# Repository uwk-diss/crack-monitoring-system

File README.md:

# Open Source Low-cost IoT Crack Monitoring Sensor System

## Introduction

Cracks in buildings and infrastructure can pose safety risks if left unmonitored. Traditional commercial solutions can be prohibitively expensive, so this project was created to provide a cost-effective alternative. Here, you will find open-source hardware designs, firmware, and backend software needed to set up a complete, network-connected crack monitoring solution.

This project provides two different sensor designs for monitoring the width of existing cracks:
- A 3D-printable long range **draw-wire sensor** using a magnetic encoder and custom PCB.
- A **digital dial indicator sensor (shahe sensor)** offering reliable and accurate readings using a off the shelf digital dial indictor of the brand SHAHE.

Both sensors are designed to operate on battery power with LoRaWAN connectivity, and a corresponding backend is provided to visualize data in real-time using MQTT, InfluxDB, and Grafana. The goal is to make structural health monitoring both accessible and affordable.

## Hardware Overview and Specifications

The main communication module for both sensors is the **Heltec WiFi LoRa 32 (V3)**, which supports a deep sleep current of approximately **21 µA**. Beyond the LoRa radio, it also integrates an OLED display and a Li-ion battery charging and protection circuit.

For the **draw-wire sensor**, the temperature, humidity, and hall angle sensors connect via I²C. Meanwhile, the **digital dial indicator sensor** uses a proprietary serial protocol, read through a customized USB OTG cable.

### Sensor specs:

| Parameter               | Draw-Wire Sensor | SHAHE Sensor |
|-------------------------|------------------|----------------|
| Measurement Range       | 55 mm            | 26 mm          |
| Resolution              | 16 µm            | 10 µm          |
| Absolute Accuracy       | 96 µm            | 10 µm          |
| Repeatability           | ±16 µm           | ±10 µm         |
| Temperature Dependence  | 5 µm/°C*         | 0 µm/°C        |
| Position drift          | yes**            | no             |
| Battery Life            | ~11 months       | ~11 months     |
| Material Cost (excluding VAT)         | ~€48.50          | ~€65           |

*Temperature compensation of the draw-wire sensor is not implemented yet.

**During a 7-week long-term test, the draw-wire sensor exhibited a permanent position offset of more than 0.1 mm. This requires further investigation.

## Communication and Backend
The sensor data is transmitted hourly via LoRaWAN. [The Things Network](https://www.thethingsnetwork.org/) can be used as a provider for the LoRaWAN backend, or a self-hosted version such as [Chripstack](https://www.chirpstack.io/).
The data must be transferred from the LoRaWAN backend to a dedicated server via MQTT and stored in a database ([InfluxDB](https://github.com/influxdata/influxdb)). A Grafana dashboard is used to visualise the data.

## Repository Overview

- **draw-wire-sensor/**  
  Contains the 3D-printable hardware design, a PCB project, and the firmware source code for the draw-wire sensor.
- **shahe-sensor/**  
  Provides the hardware documentation and firmware to integrate the commercially available Shahe digital indicator.
- **backend/**  
  Contains Docker configurations, scripts, and a Grafana dashboard for storing, processing, and visualizing crack measurements.

More information and detailed assembly as well as usage instructions can be found in the respective subfolders.

## Credits

We would like to acknowledge the following open-source software libraries and frameworks that have made this project possible:
- [heltec_esp32_lora_v3 by Rop Gonggrijp](https://github.com/ropg/heltec_esp32_lora_v3) for providing the easy to use Heltec WiFi LoRa 32(V3) library
- [LoRaWAN_ESP32 by Rop Gonggrijp](https://github.com/ropg/LoRaWAN_ESP32) for LoRaWAN persistence handling
- [RadioLib](https://github.com/jgromes/RadioLib) for LoRaWan communication handling
- [PlatformIO](https://platformio.org/) for easy firmware development and deployment
- [Arduino Core](https://github.com/arduino/Arduino) for base microcontroller support
- [Docker](https://www.docker.com/) for containerization
- [Grafana](https://grafana.com/) for data visualization
- [InfluxDB](https://www.influxdata.com/) for time-series database storage

## Disclaimer

This Project is not completely finalized and may undergo changes. Use at your own risk.

## License

This project is available under the [MIT License](./LICENSE).

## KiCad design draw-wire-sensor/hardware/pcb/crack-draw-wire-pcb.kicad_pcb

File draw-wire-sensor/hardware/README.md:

# Draw-Wire Crack Sensor Hardware

## Draw-Wire Sensor
[3D-model Onshape Link](https://cad.onshape.com/documents/727012fc8109642ef30e330c/w/04f195b811331b23b33eb80b/e/cc3c6dd55492ae3cabf4f177?renderMode=0&uiState=67e1a618d2f76412aff66577)

### Functionality

### Materials
- 3D printed parts (Spool, BearingHolder1, BearingHolder2)
- Hall sensor PCB
- 8x16x5 mm ball bearing
- 0.2x5x420 mm spring
- 2 mm steel rod (2 pcs. 12 mm, 2 pcs. 8 mm) e.g. a bicycle spoke
- 0.5 mm steel wire (100 mm)
- Diametrical magnet (6 mm diameter, 1 mm thick)
- M4x8 button head screw and M4 washer
- M4x30 screws (4 pcs.)
- Single screw terminal as wire stopper

### Tools
- 3D Printer
- Soldering iron, solder, flux, and solder wick
- Round-nose pliers
- Tongue-and-groove pliers
- 2 mm drill bit

### Assembly
1. Assemble the PCB.
2. Print the parts (100% infill, 0.1 mm layer height).
3. Insert (and glue) the magnet into the spool with maximum precision.
4. Press-fit the bearings into the bearing-holders.
5. Press-fit the steel rods into the spool and upper bearing-holder (you may need to slightly drill out the holes beforehand).
6. Bend the spring as shown in the picture using round-nose pliers.
7. Insert the spool and then the spring.
8. Add the lower bearing-holder and slightly tighten the button head screw on the bottom of the spool.

## Enclosure
[3D-model Onshape Link](https://cad.onshape.com/documents/93da92487be01dacccf96228/w/5f335a3fbf208dbb23918342/e/3e6e6e181994376e8e597439?renderMode=0&uiState=67e194bb183653275da219e5)

### Materials
- 3D printed enclosure (ASA)
- Acrylic glass (2 mm) or 3D printed lid
- Short M3 inserts (8 pcs.)
- Short M4 inserts (4 pcs.)
- Short M2 inserts (2 pcs.)
- M3x6 screws (8 pcs.)
- M2x5 screws (2 pcs.)
- EPDM sealing cord (255 mm)
- Rubber grommet
- Acrylic paint / conformal coating / 3D-print sealant
- Silicone grease

### Tools
- 3D Printer
- Soldering iron
- 3.5 mm drill bit and drill
- Cutter knife

### Assembly
1. Print the enclosure (100% infill, 0.15 mm layer height).
2. Seal the print with spray paint.
3. Print the lid template (0.5 mm).
4. Transfer the template to acrylic glass and cut out the outlines.
5. Drill 3.5 mm screw holes in the lid.
6. Use a soldering iron to melt in the inserts.
7. Lubricate the seal and the grommet with silicone grease and insert them.

## Additional information
- With a longer string multiple parallel cracks can be monitored at once

## Future Improvements / To-Dos / Ideas
- Create a parametric 3D design for the draw-wire sensor and the enclosure using FreeCAD.
- Add a 3D printable adapter for standalone use of the draw-wire sensor with standard AS5600/MT6701 modules.
- Investigate the impact of hall sensor magnet alignment on accuracy and hysteresis.
- Further investigate the permanent drift of the sensor position

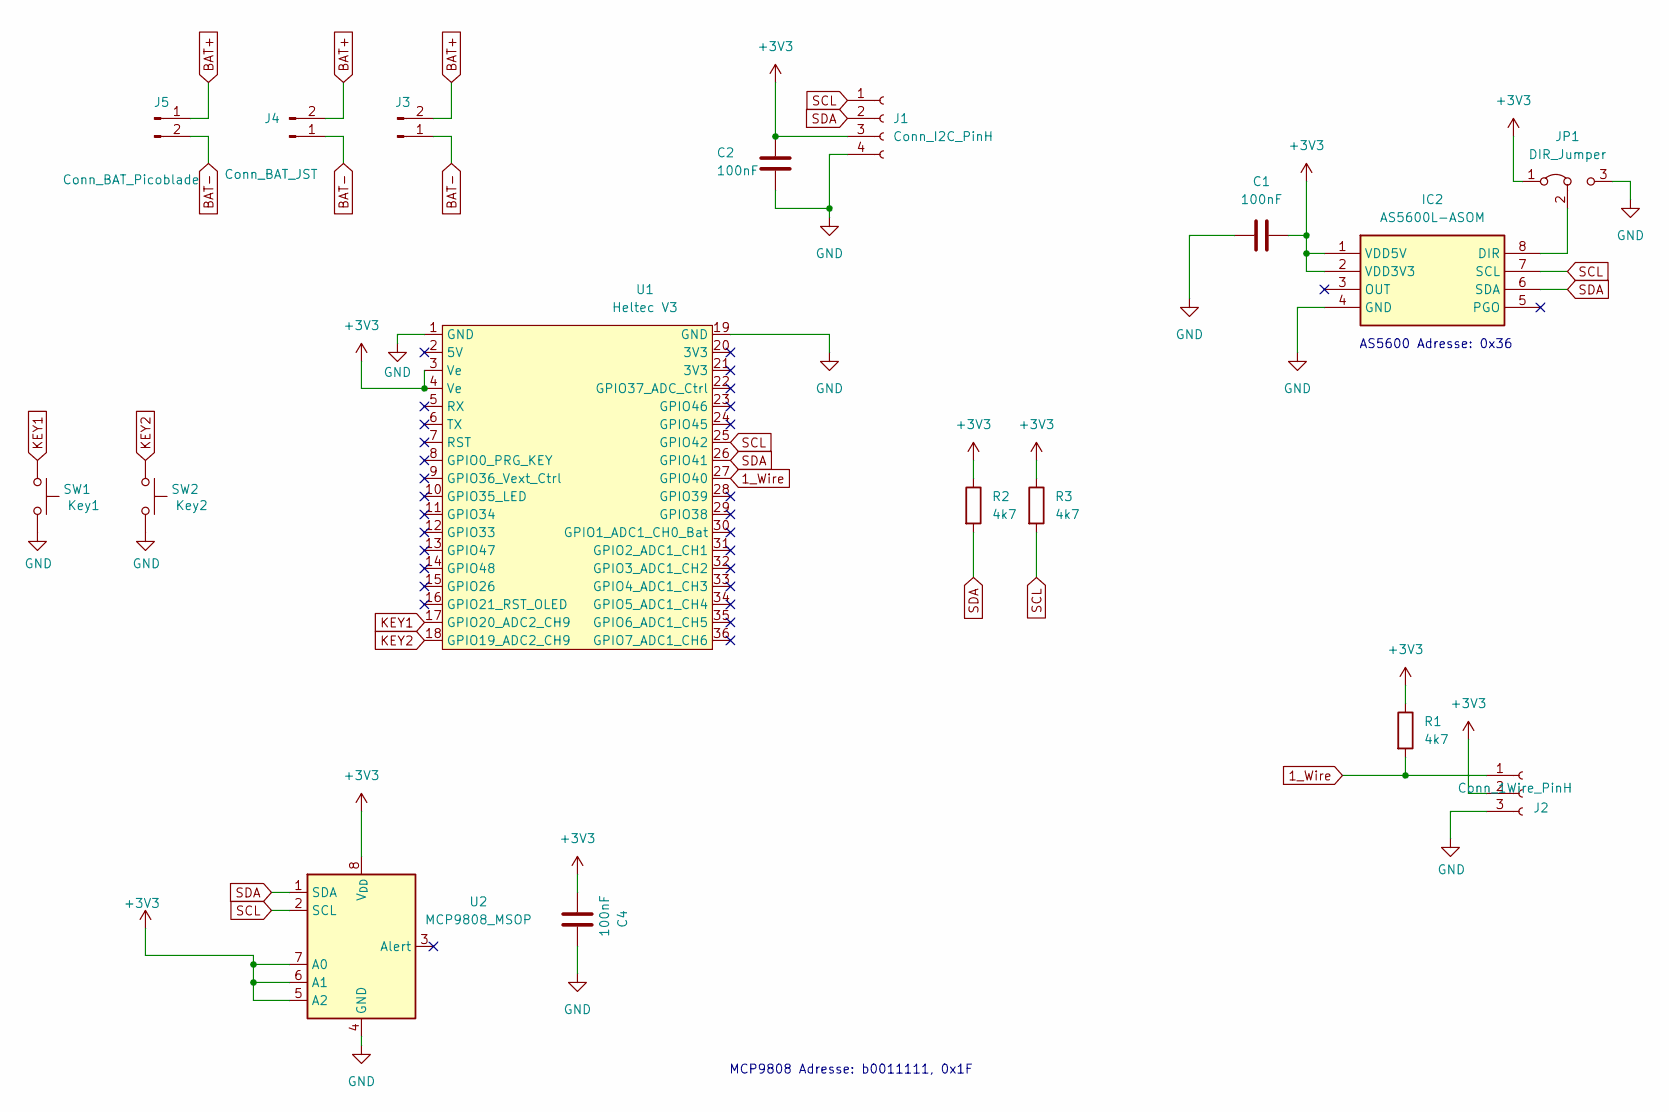
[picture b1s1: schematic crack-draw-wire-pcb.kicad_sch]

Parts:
C1, C2, C4: 100nF; C_0603_1608Metric
IC2: AS5600L-ASOM; SOIC127P600X175-8N; Mouser Part Number 985-AS5600L-ASOM
J1: Conn_I2C_PinH; PinHeader_1x04_P2.54mm_Vertical
J2: Conn_1Wire_PinH; PinHeader_1x03_P2.54mm_Vertical
J3, J4: Conn_BAT_JST; JST_PH_B2B-PH-K_1x02_P2.00mm_Vertical
J5: Conn_BAT_Picoblade; Molex_PicoBlade_53047-0210_1x02_P1.25mm_Vertical
JP1: DIR_Jumper; SolderJumper-3_P1.3mm_Open_Pad1.0x1.5mm
R1, R2, R3: 4k7; R_0603_1608Metric
SW1: Key1; SW_Push_SPST_NO_Alps_SKRK
SW2: Key2; SW_Push_SPST_NO_Alps_SKRK
U1: Heltec V3; Heltec_Wifi_LoRa_V3
U2: MCP9808_MSOP; MSOP-8_3x3mm_P0.65mm

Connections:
1_Wire: J2.1, R1.2, U1.27 (GPIO40)
+3V3: C1.2, C2.2, C4.1, IC2.1 (VDD5V), IC2.2 (VDD3V3), J1.3, J2.2, JP1.1 (A), R1.1, R2.1, R3.1, U1.3 (Ve), U1.4 (Ve), U2.5 (A2), U2.6 (A1), U2.7 (A0), U2.8 (V_{DD})
BAT+: J3.2, J4.2, J5.1
BAT-: J3.1, J4.1, J5.2
GND: C1.1, C2.1, C4.2, IC2.4 (GND), J1.4, J2.3, JP1.3 (B), SW1.1, SW2.1, U1.1 (GND), U1.19 (GND), U2.4 (GND)
KEY1: SW1.2, U1.17 (GPIO20_ADC2_CH9)
KEY2: SW2.2, U1.18 (GPIO19_ADC2_CH9)
unnamed: IC2.8 (DIR), JP1.2 (C)
SCL: IC2.7 (SCL), J1.1, R3.2, U1.25 (GPIO42), U2.2 (SCL)
SDA: IC2.6 (SDA), J1.2, R2.2, U1.26 (GPIO41), U2.1 (SDA)

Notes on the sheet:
MCP9808 Adresse: b0011111, 0x1F
AS5600 Adresse: 0x36

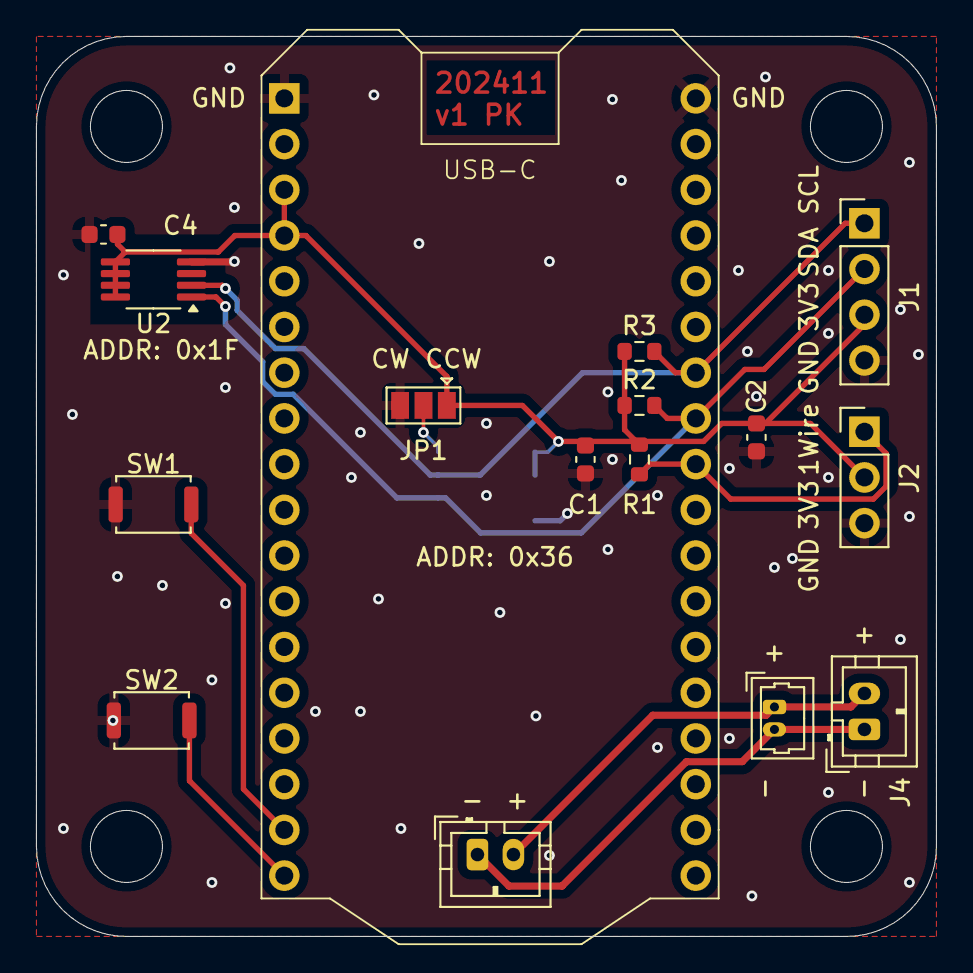
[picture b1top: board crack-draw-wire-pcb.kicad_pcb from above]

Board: 2 copper layers, 50.0 x 50.0 mm, 17 parts (1 on the bottom side), 10 nets.

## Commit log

2025-03-26 initial
